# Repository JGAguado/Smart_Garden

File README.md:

[![Documentation Status][documentation-shield]][documentation]
[![GitHub Release][releases-shield]][releases]
[![License][license-shield]](LICENSE)
[![BuyIt][buyit-shield]][tindie]

[![Project Maintenance][maintenance-shield]][maintenance]
[![BuyMeCoffee][buymecoffee-shield]][buymecoffee]

# Smart Garden
The Smart Garden is an electronic board based on the ESP32 capable of controlling a combination of 4 irrigation valves and/or water pumps, 
supporting AC & DC voltages

## Project tree
---
<li><a href="./Design/">Design</a></li>
<li><a href="./Documentation/">Documentation</a></li>

<li><a href="./README.md">README.md</a></li>

[documentation-shield]: https://readthedocs.org/projects/smart-garden/badge/?version=latest&style=for-the-badge
[documentation]: https://smart-garden.readthedocs.io/en/latest/

[releases-shield]: https://img.shields.io/github/release/JGAguado/Smart_Garden.svg?style=for-the-badge
[releases]: https://github.com/JGAguado/Smart_Garden/releases

[license-shield]: https://img.shields.io/badge/License-CC%20BY--NC--SA%204.0-lightgrey.svg?style=for-the-badge

[maintenance-shield]: https://img.shields.io/badge/maintainer-J.%20G.%20Aguado-blue.svg?style=for-the-badge
[maintenance]: https://github.com/JGAguado

[buymecoffee-shield]: https://img.shields.io/badge/buy%20me%20a%20coffee-support-yellow.svg?style=for-the-badge
[buymecoffee]: https://www.buymeacoffee.com/J.G.Aguado

[buyit-shield]: https://img.shields.io/badge/get%20it%20on-tindie-247d84.svg?style=for-the-badge
[tindie]: https://www.tindie.com/products/jgaguado/smart-garden/

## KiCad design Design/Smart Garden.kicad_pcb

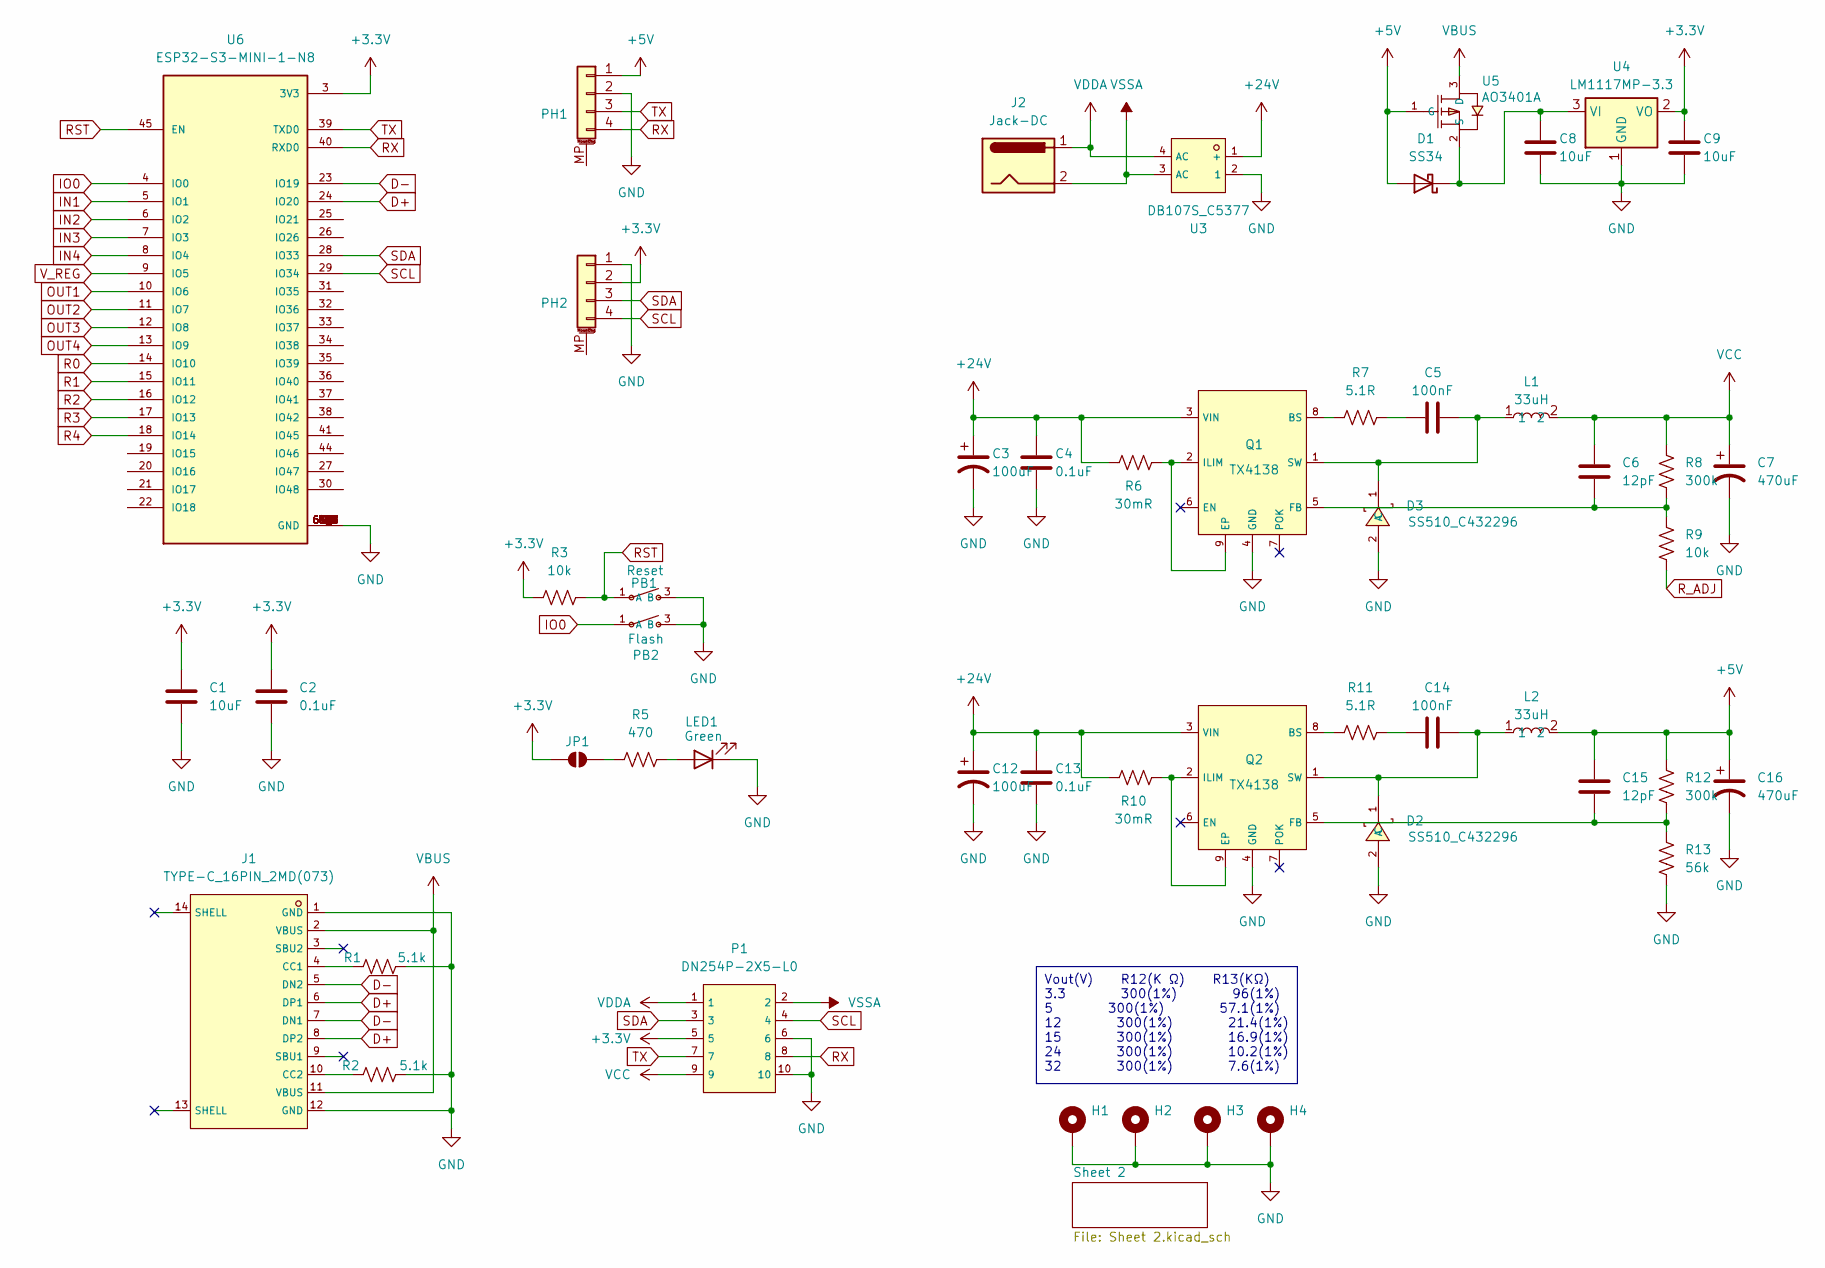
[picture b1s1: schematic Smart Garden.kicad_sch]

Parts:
C1, C8, C9: 10uF; C_0603_1608Metric
C2, C4, C13: 0.1uF; C_0603_1608Metric
C3, C12: 100uF; CP_Elec_6.3x7.7; LCSC C487070
C5, C14: 100nF; C_0603_1608Metric
C6, C15: 12pF; C_0603_1608Metric
C7, C16: 470uF; CP_Elec_10x10; LCSC C724672
D1: SS34; D_SMA
D2, D3: SS510_C432296; SMA_L4.4-W2.8-LS5.4-RD; LCSC C432296
H1, H2, H3, H4: MountingHole_Pad; MountingHole_3.5mm_Pad_Via
J1: TYPE-C_16PIN_2MD(073); USB-C-SMD_TYPE-C-6PIN-2MD-073; LCSC C2765186
J2: Jack-DC; BarrelJack_Horizontal
JP1: SolderJumper_2_Bridged; SolderJumper-2_P1.3mm_Open_RoundedPad1.0x1.5mm
L1, L2: 33uH; IND-SMD_L12.0-W12.0_CDRH127NP; LCSC C167264
LED1: Green; LED_0603_1608Metric
P1: DN254P-2X5-L0; IDC-SMD_10P-P2.54-V-R2-C5-S9.50; LCSC C4749178
PB1: Reset; SW-SMD_4P-L4.5-W4.5-P3.00-LS6.8; LCSC C5342982
PB2: Flash; SW-SMD_4P-L4.5-W4.5-P3.00-LS6.8; LCSC C5342982
PH1, PH2: Conn_01x04_MountingPin; PinHeader_1x04_P2.54mm_Vertical
Q1, Q2: TX4138; SOIC-8_L4.9-W3.9-P1.27-LS6.0-BL-EP; LCSC C329267
R1, R2: 5.1k; R_0603_1608Metric
R3, R9: 10k; R_0603_1608Metric
R5: 470; R_0603_1608Metric
R6, R10: 30mR; R_1206_3216Metric
R7, R11: 5.1R; R_0603_1608Metric
R8, R12: 300k; R_0603_1608Metric
R13: 56k; R_0603_1608Metric
U3: DB107S_C5377; DBS_L8.2-W6.4-P5.10-LS10.0-BL; LCSC C5377
U4: LM1117MP-3.3; SOT-223-3_TabPin2
U5: AO3401A; SOT-23_L2.9-W1.3-P1.90-LS2.4-BR; LCSC C15127
U6: ESP32-S3-MINI-1-N8; XCVR_ESP32-S3-MINI-1-N8; PARTREV v0.6

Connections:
+3.3V: C1.1, C2.1, C9.1, JP1.1 (A), P1.5, PH2.2, R3.1, U4.2 (VO), U6.3 (3V3); also elsewhere on the board
+5V: C15.1, C16.1, D1.2 (A), L2.2, PH1.1, R12.2, U5.1 (G); also elsewhere on the board
+24V: C3.1, C4.1, C12.1, C13.1, Q1.3 (VIN), Q2.3 (VIN), R6.1, R10.1, U3.1 (+)
D+: J1.6 (DP1), J1.8 (DP2), U6.24 (IO20)
D-: J1.5 (DN2), J1.7 (DN1), U6.23 (IO19)
GND: C1.2, C2.2, C3.2, C4.2, C7.2, C8.2, C9.2, C12.2, C13.2, C16.2, D2.2 (A), D3.2 (A), H1.1, H2.1, H3.1, H4.1, J1.1 (GND), J1.12 (GND), LED1.1 (K), P1.6, P1.10, PB1.3 (B), PB2.3 (B), PH1.2, PH2.1, Q1.4 (GND), Q2.4 (GND), R1.2, R2.2, R13.1, U3.2 (1), U4.1 (GND), U6.1 (GND), U6.2 (GND), U6.42 (GND), U6.43 (GND), U6.46 (GND), U6.47 (GND), U6.48 (GND), U6.49 (GND), U6.50 (GND), U6.51 (GND), U6.52 (GND), U6.53 (GND), U6.54 (GND), U6.55 (GND), U6.56 (GND), U6.57 (GND), U6.58 (GND), U6.59 (GND), U6.60 (GND), U6.61 (GND), U6.61_1 (GND), U6.61_2 (GND), U6.61_3 (GND), U6.61_4 (GND), U6.61_5 (GND), U6.61_6 (GND), U6.61_7 (GND), U6.61_8 (GND), U6.62 (GND), U6.63 (GND), U6.64 (GND), U6.65 (GND); also elsewhere on the board
IN1: U6.5 (IO1); also elsewhere on the board
IN2: U6.6 (IO2); also elsewhere on the board
IN3: U6.7 (IO3); also elsewhere on the board
IN4: U6.8 (IO4); also elsewhere on the board
IO0: PB2.1 (A), U6.4 (IO0)
unnamed: C5.2, R7.2
unnamed: C14.2, R11.2
unnamed: C8.1, D1.1 (K), U4.3 (VI), U5.2 (S)
unnamed: C14.1, D2.1 (C), L2.1, Q2.1 (SW)
unnamed: C5.1, D3.1 (C), L1.1, Q1.1 (SW)
unnamed: J1.4 (CC1), R1.1
unnamed: J1.10 (CC2), R2.1
unnamed: JP1.2 (B), R5.1
unnamed: LED1.2 (A), R5.2
unnamed: Q1.8 (BS), R7.1
unnamed: Q1.2 (ILIM), Q1.9 (EP), R6.2
unnamed: C6.2, Q1.5 (FB), R8.1, R9.2
unnamed: Q2.8 (BS), R11.1
unnamed: Q2.2 (ILIM), Q2.9 (EP), R10.2
unnamed: C15.2, Q2.5 (FB), R12.1, R13.2
OUT1: U6.10 (IO6); also elsewhere on the board
OUT2: U6.11 (IO7); also elsewhere on the board
OUT3: U6.12 (IO8); also elsewhere on the board
OUT4: U6.13 (IO9); also elsewhere on the board
R0: U6.14 (IO10); also elsewhere on the board
R1: U6.15 (IO11); also elsewhere on the board
R2: U6.16 (IO12); also elsewhere on the board
R3: U6.17 (IO13); also elsewhere on the board
R4: U6.18 (IO14); also elsewhere on the board
RST: PB1.1 (A), R3.2, U6.45 (EN)
RX: P1.8, PH1.4, U6.40 (RXD0)
R_ADJ: R9.1; also elsewhere on the board
SCL: P1.4, PH2.4, U6.29 (IO34); also elsewhere on the board
SDA: P1.3, PH2.3, U6.28 (IO33); also elsewhere on the board
TX: P1.7, PH1.3, U6.39 (TXD0)
VBUS: J1.2 (VBUS), J1.11 (VBUS), U5.3 (D)
VCC: C6.1, C7.1, L1.2, P1.9, R8.2; also elsewhere on the board
VDDA: J2.1, P1.1, U3.4 (AC); also elsewhere on the board
VSSA: J2.2, P1.2, U3.3 (AC); also elsewhere on the board
V_REG: U6.9 (IO5); also elsewhere on the board

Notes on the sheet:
Vout(V) R12(K Ω) R13(KΩ) 3.3 300(1%) 96(1%) 5 300(1%) 57.1(1%) 12 300(1%) 21.4(1%) 15 300(1%) 16.9(1%) 24 300(1%) 10.2(1%) 32 300(1%) 7.6(1%)

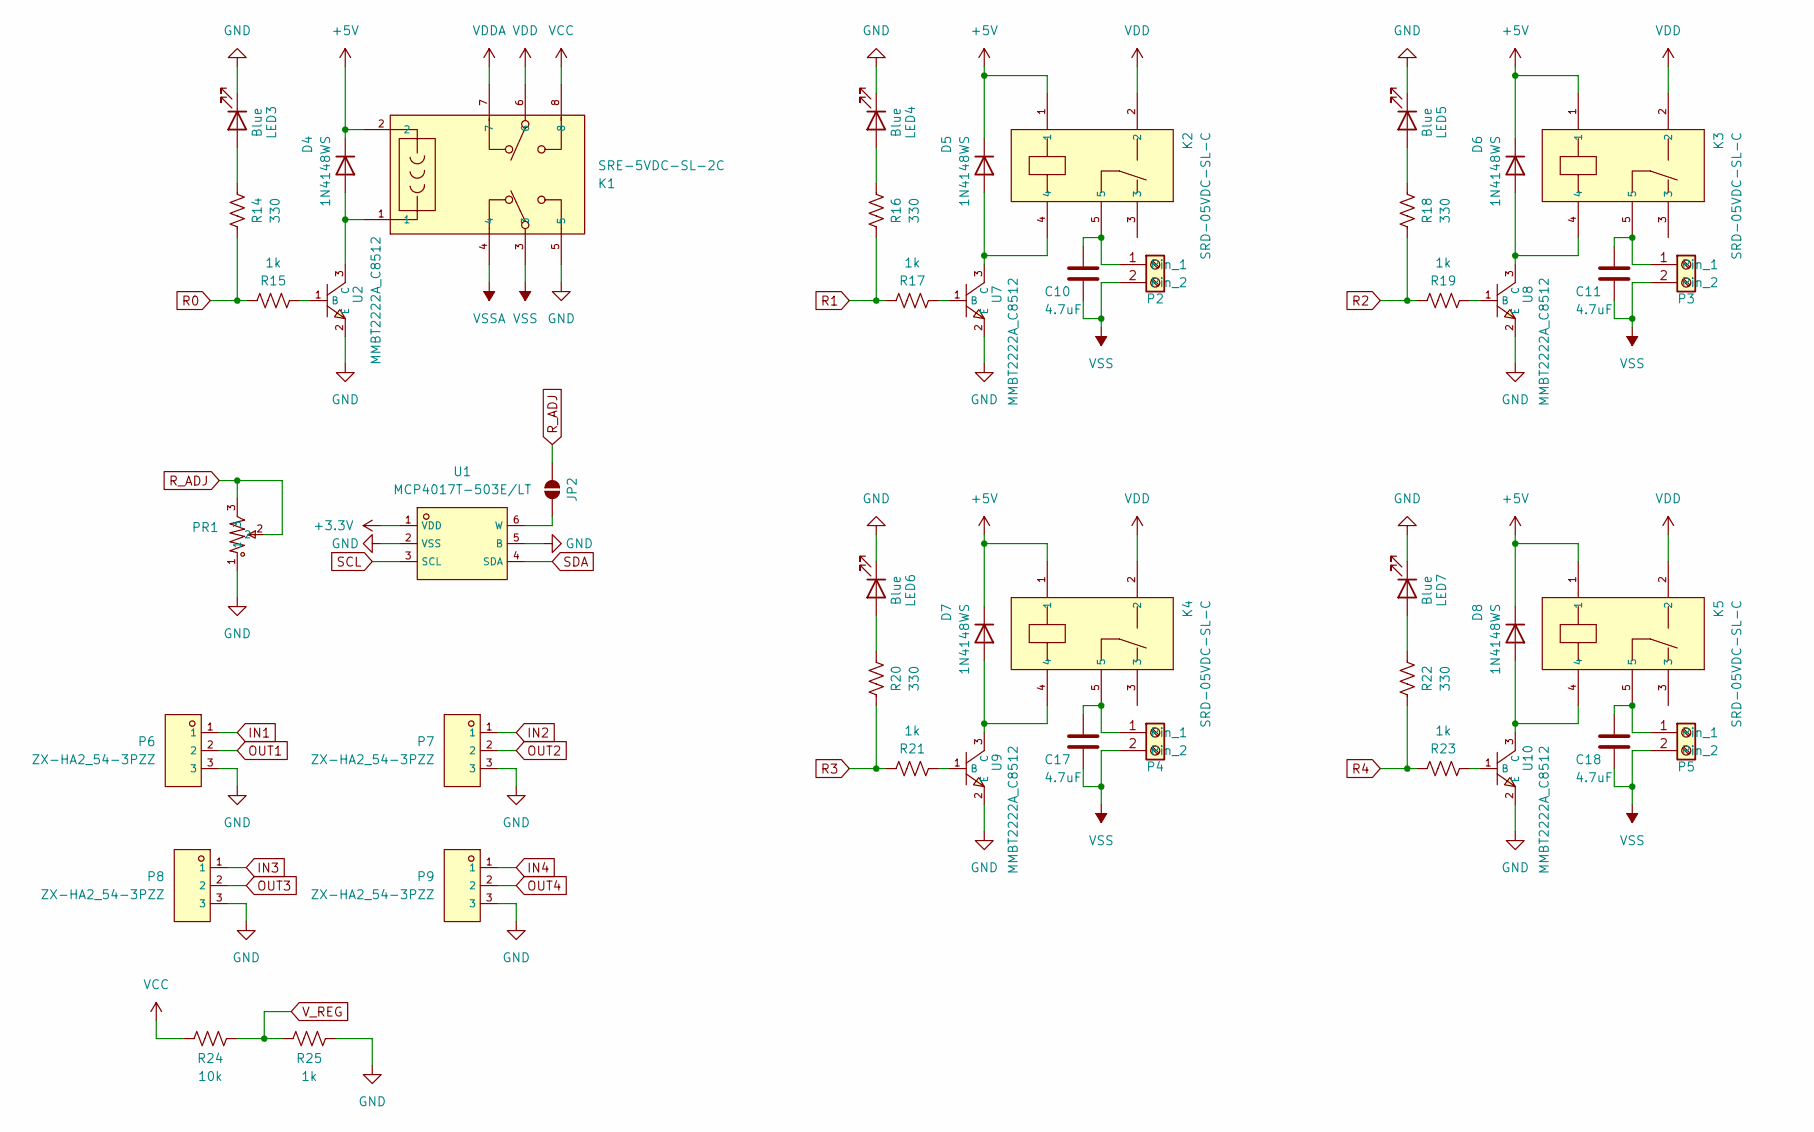
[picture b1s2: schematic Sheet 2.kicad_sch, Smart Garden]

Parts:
C10, C11, C17, C18: 4.7uF; C_0603_1608Metric
D4, D5, D6, D7, D8: 1N4148WS; D_SOD-323
JP2: SolderJumper_2_Bridged; SolderJumper-2_P1.3mm_Open_RoundedPad1.0x1.5mm
K1: SRE-5VDC-SL-2C; RELAY-TH_SRE-XXVDC-SL-2C
K2, K3, K4, K5: SRD-05VDC-SL-C; RELAY-TH_SRD-XXVDC-XL-C; LCSC C35449
LED3, LED4, LED5, LED6, LED7: Blue; LED_0603_1608Metric
P2, P3, P4, P5: WJ300V-5_0-2P; CONN-TH_2P-P5.00_WJ300V-5.00-2P; LCSC C8385
P6, P7, P8, P9: ZX-HA2_54-3PZZ; CONN-TH_XH-3A; LCSC C7429615
PR1: 3296W-1-103; RES-ADJ-TH_3P-L10.0-W10.0-P2.50-L; LCSC C118954
R14, R16, R18, R20, R22: 330; R_0603_1608Metric
R15, R17, R19, R21, R23, R25: 1k; R_0603_1608Metric
R24: 10k; R_0603_1608Metric
U1: MCP4017T-503E/LT; SC-70-6_L2.0-W1.3-P0.65-LS2.1-BL; LCSC C478095
U2, U7, U8, U9, U10: MMBT2222A_C8512; SOT-23-3_L2.9-W1.3-P1.90-LS2.4-BR; LCSC C8512

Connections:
+3.3V: U1.1 (VDD); also elsewhere on the board
+5V: D4.1 (K), D5.1 (K), D6.1 (K), D7.1 (K), D8.1 (K), K1.2, K2.1, K3.1, K4.1, K5.1; also elsewhere on the board
GND: K1.5, LED3.1 (K), LED4.1 (K), LED5.1 (K), LED6.1 (K), LED7.1 (K), P6.3, P7.3, P8.3, P9.3, PR1.1, R25.2, U1.2 (VSS), U1.5 (B), U2.2 (E), U7.2 (E), U8.2 (E), U9.2 (E), U10.2 (E); also elsewhere on the board
IN1: P6.1; also elsewhere on the board
IN2: P7.1; also elsewhere on the board
IN3: P8.1; also elsewhere on the board
IN4: P9.1; also elsewhere on the board
unnamed: D4.2 (A), K1.1, U2.3 (C)
unnamed: D5.2 (A), K2.4, U7.3 (C)
unnamed: D6.2 (A), K3.4, U8.3 (C)
unnamed: D7.2 (A), K4.4, U9.3 (C)
unnamed: D8.2 (A), K5.4, U10.3 (C)
unnamed: JP2.2 (B), U1.6 (W)
unnamed: LED3.2 (A), R14.2
unnamed: LED4.2 (A), R16.2
unnamed: LED5.2 (A), R18.2
unnamed: LED6.2 (A), R20.2
unnamed: LED7.2 (A), R22.2
unnamed: C10.1, K2.5, P2.1
unnamed: C11.1, K3.5, P3.1
unnamed: C17.1, K4.5, P4.1
unnamed: C18.1, K5.5, P5.1
unnamed: R15.1, U2.1 (B)
unnamed: R17.1, U7.1 (B)
unnamed: R19.1, U8.1 (B)
unnamed: R21.1, U9.1 (B)
unnamed: R23.1, U10.1 (B)
OUT1: P6.2; also elsewhere on the board
OUT2: P7.2; also elsewhere on the board
OUT3: P8.2; also elsewhere on the board
OUT4: P9.2; also elsewhere on the board
R0: R14.1, R15.2; also elsewhere on the board
R1: R16.1, R17.2; also elsewhere on the board
R2: R18.1, R19.2; also elsewhere on the board
R3: R20.1, R21.2; also elsewhere on the board
R4: R22.1, R23.2; also elsewhere on the board
R_ADJ: JP2.1 (A), PR1.2, PR1.3; also elsewhere on the board
SCL: U1.3 (SCL); also elsewhere on the board
SDA: U1.4 (SDA); also elsewhere on the board
VCC: K1.8, R24.1; also elsewhere on the board
VDD: K1.6, K2.2, K3.2, K4.2, K5.2
VDDA: K1.7; also elsewhere on the board
VSS: C10.2, C11.2, C17.2, C18.2, K1.3, P2.2, P3.2, P4.2, P5.2
VSSA: K1.4; also elsewhere on the board
V_REG: R24.2, R25.1; also elsewhere on the board

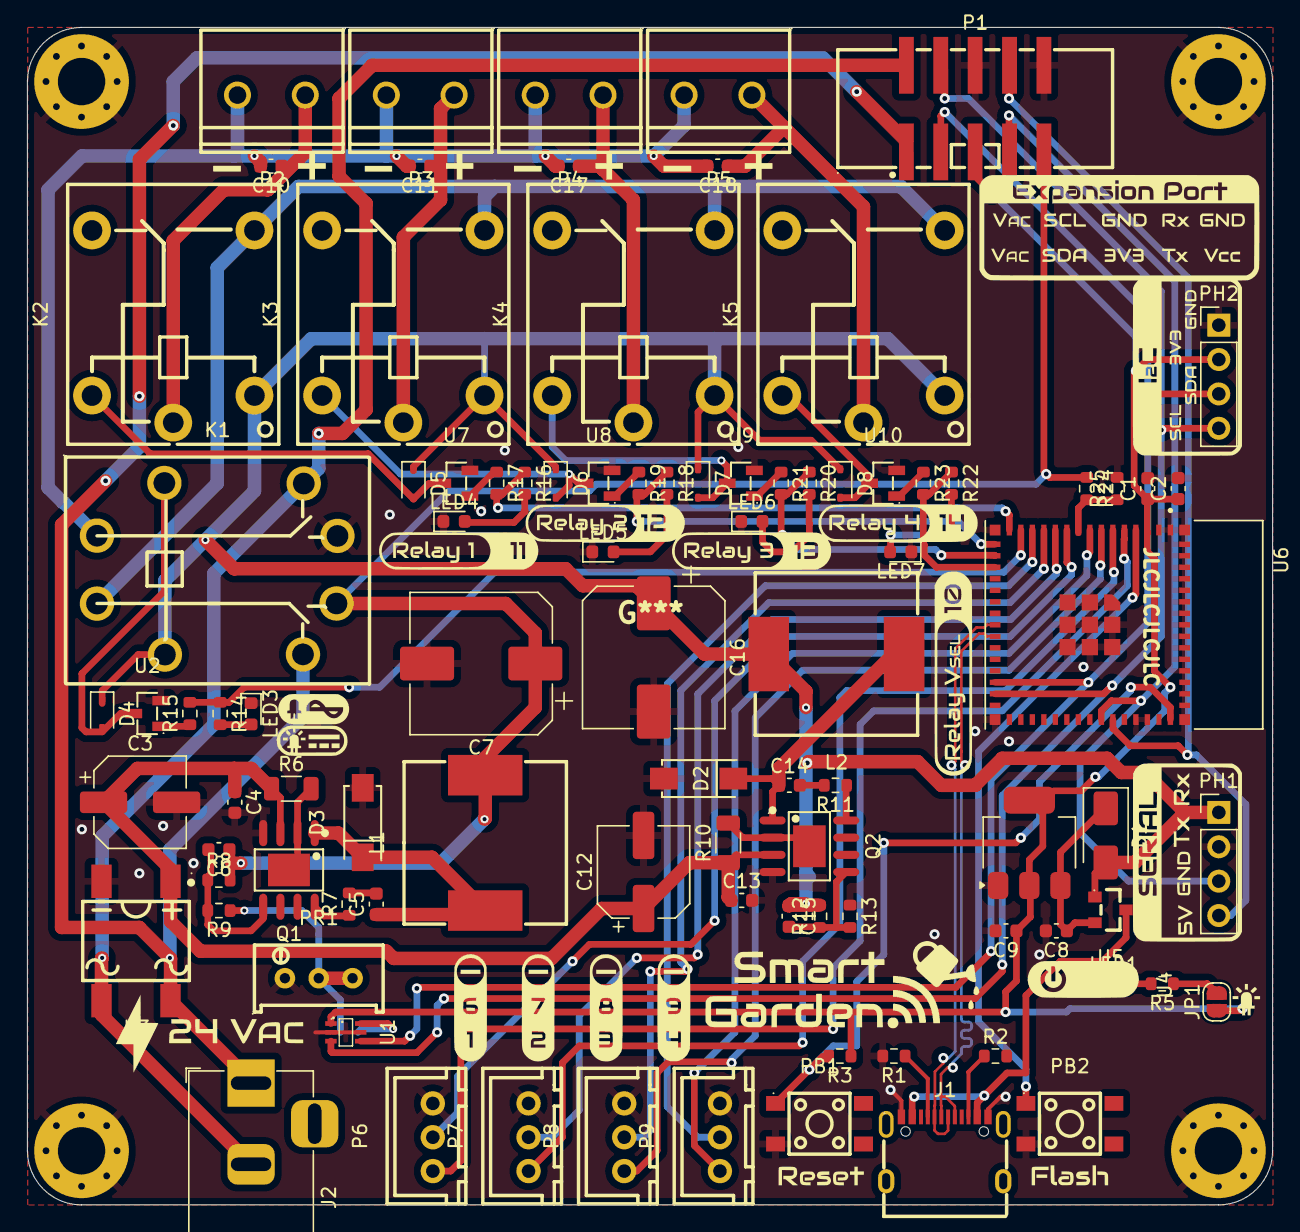
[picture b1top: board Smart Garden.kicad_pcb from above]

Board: 2 copper layers, 92.0 x 87.0 mm, 97 parts (1 on the bottom side), 68 nets.

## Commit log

2022-04-13 Added silkscreen designs
2022-04-13 Added design files
2022-04-13 Added documentation
2022-04-24 Removed dimension drawings from brd and reloaded images
2022-05-11 Updated documentation adding Measures.pdf and Datasheets
2022-08-09 First commit to the CP2102 branch with schematic and a first layout of the CP2102
2022-08-20 First commit to the CP2102 branch
2022-09-26 Updated design files
2022-09-26 Updated documentation files
2022-10-06 Updated Silkscreen
2022-10-23 Updated Documentation/Images
2022-11-01 docs
2022-11-08 Updated Images
2023-02-05 docs/requirements.txt
2023-02-23 Silkscreen fixed
2023-03-15 Updated configuration.yaml
2024-07-02 Added V2R1 design files
2024-07-02 Added Silkscreen
2024-07-02 Images
2024-07-03 schematics
2024-07-07 Updated image
2024-08-05 First draft
